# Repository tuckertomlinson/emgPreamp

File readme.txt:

#Boilerplate:
The files in this repository are my attempt to produce a high-quailty,
buffering amplifier for EMG signals in the laboratory environment. I
am NOT a hardware designer by trade and have not necessarily tested
any of the supplied files for my own purposes, much less yours. I 
make no garauntees that these circuits will be useful or even 
functional.

It is important to also note: I have not designed these
to comply with any FDA standards. Any compliance with said standards
is purely coincidental. These designs are inteded for animal research
and are NOT fit for human recordings in the clinical environment. 

If you choose to use these designs, it is incumbent on you to evaluate
the schematics and test them to ensure they are adequate, in both 
performance and safety, for your task.

I make no promise of support, however, you are welcome to shoot me
an email if you want to use these designs. I might be able to answer
some simple questions.

#The project:
-I need to record 24 differential EMG signals from intramuscular wires
-My signals of interest are in the +/-10mV range
-My ADC system has a +/-5V range, and is remote from the signal source
-I need to buffer and amplify my signals at the source to avoid line
artifacts in my recordings
-The source of the signal is a 50pin samtec 0.05" connector, which I 
	want to convert to something sane like a DB style connector
	so I can use standard cables with my amplified signals

#the solution:
-Signal source connects to a backplane card
-backplane has 6x16pin header sockets 
-each header socket accepts a daughter card that contains 4 differential channels
-Connection to external systems is via DB37 connector
  -24 signal out lines
  -GND and external power in (optional)
  -reference rail out
-daughter cards take:
  - 8 lines of input signal (4 differential signals), 
  - a ground rail, 
  - a power rail
    -the power rail should be in the 5-18V range
  -and a reference rail.
    -the reference rail should be ~ halfway between the ground and power rails
-daughter cards output:
  -4 lines of amplified differential signal centered on the reference rail
-Backplane has a 5pin header socket that is the source of the ground, power and reference rails
  -power connection to external systems will depend on the DAC format you use
  -for a 0V centered ADC (e.g. +/-5V), isolate the ground and power rails from the world, and short the reference to the ADC ground
  -for a positive biased ADC (e.g. 0-10V), connect the ground rail to the DAC ground, and the reference rail to one of the ADC inputs
    -logging the voltage of VRef allows you to subtract in software, recovering the true differential signal
  -The easiest power solution is to simply use 2x 9V batteries in series
    -Power rail is 18V, reference rail is 9V
  -included in the project is a schematic for a power conditioning card
    -card takes in 12-15V power
    -Isolates to internal 12V rail via switchmode isolation supply
    -Uses filters and linear regulators to supply 10V power rail and 5v reference rail to backplane
    -power rail, backplane ground and reference rail are isolated from the supplied power.

The circuit schematics for this project are built in Eagle. 
I have tried to label the lines in each PCB in a sane way, so it should be possible to sort out what's going on. 

In some cases I have needed to create a custom part based on other 
existing libraries in order to get the correct footprint and pinout. 
I have not explicitly included those libraries in this project.

Currently the backplane and daughter cards are tested and functioning as designed. With implanted EMG wires it is common to see single motor unit acticity in the EMG signal. The power-conditioning board is not yet tested

Tucker Tomlinson
tuckertomlinson@gmail.com
Jan 25 2017

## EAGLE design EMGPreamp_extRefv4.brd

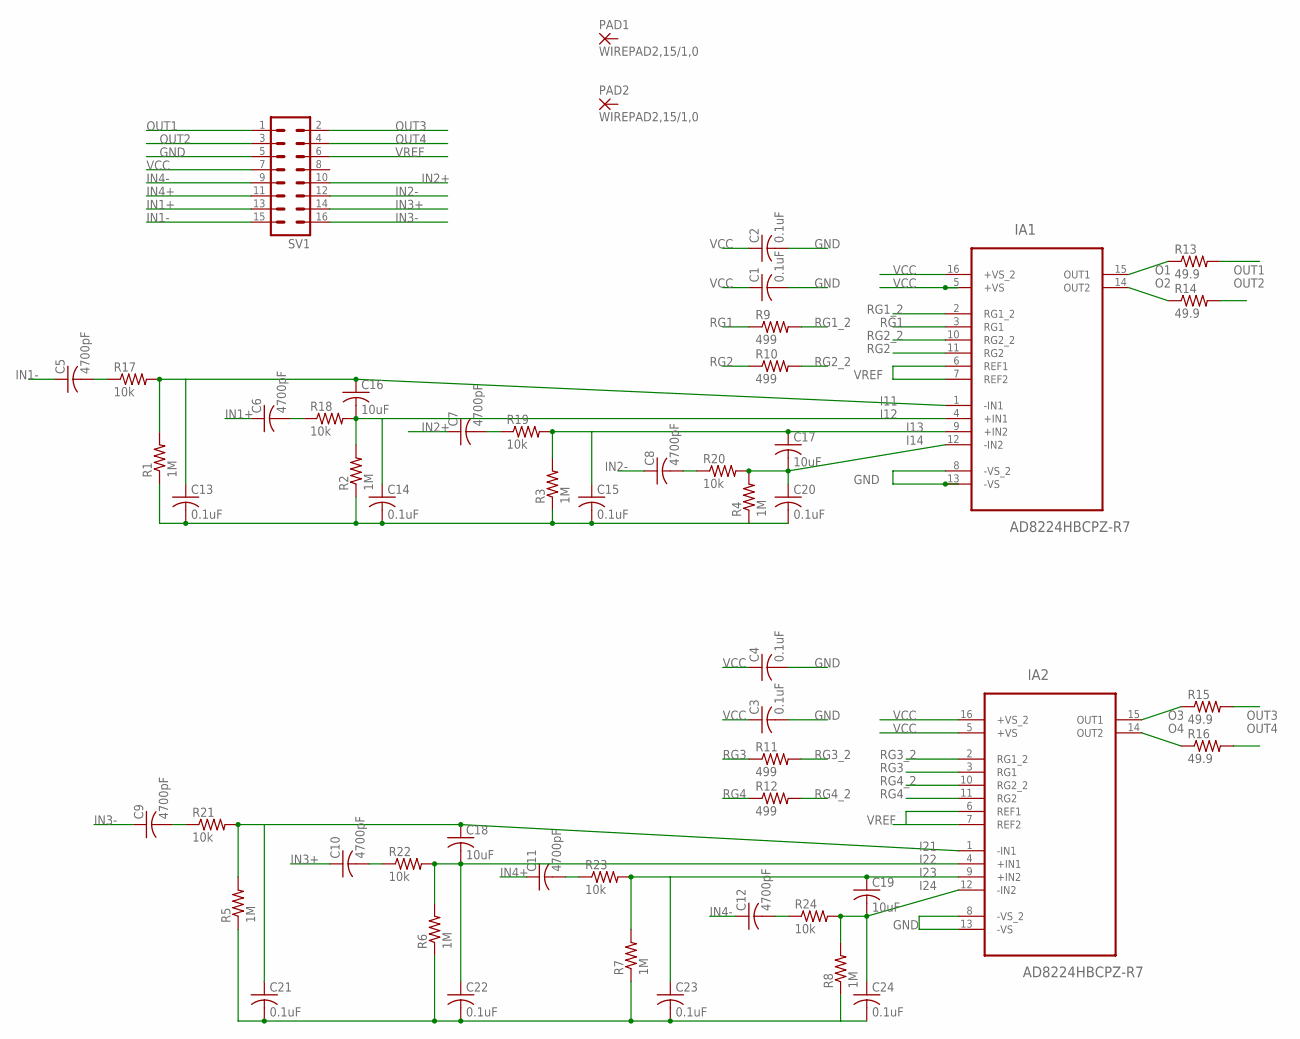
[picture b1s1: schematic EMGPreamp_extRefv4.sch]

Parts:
C1, C2, C3, C4, C13, C14, C15, C20, C21, C22, C23, C24: 0.1uF; C0805
C5, C6, C7, C8, C9, C10, C11, C12: 4700pF; C0805
C16, C17, C18, C19: 10uF; C0805
IA1, IA2: AD8224HBCPZ-R7; QFN65P400X400X100-16N
PAD1, PAD2: WIREPAD2,15/1,0; 2,15/1,0
R1, R2, R3, R4, R5, R6, R7, R8: 1M; R0805
R9, R10, R11, R12: 499; R0805
R13, R14, R15, R16: 49.9; R0805
R17, R18, R19, R20, R21, R22, R23, R24: 10k; R0805
SV1: MA08-2W

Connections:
GND: C1.2, C2.2, C3.2, C4.2, C13.2, C14.2, C15.2, C20.2, C21.2, C22.2, C23.2, C24.2, IA1.8 (-VS_2), IA1.13 (-VS), IA2.8 (-VS_2), IA2.13 (-VS), R1.1, R2.1, R3.1, R4.1, R5.1, R6.1, R7.1, R8.1, SV1.5
I11: C13.1, C16.1, IA1.1 (-IN1), R1.2, R17.2
I12: C14.1, C16.2, IA1.4 (+IN1), R2.2, R18.2
I13: C15.1, C17.1, IA1.9 (+IN2), R3.2, R19.2
I14: C17.2, C20.1, IA1.12 (-IN2), R4.2, R20.2
I21: C18.1, C21.1, IA2.1 (-IN1), R5.2, R21.2
I22: C18.2, C22.1, IA2.4 (+IN1), R6.2, R22.2
I23: C19.1, C23.1, IA2.9 (+IN2), R7.2, R23.2
I24: C19.2, C24.1, IA2.12 (-IN2), R8.2, R24.2
IN1+: C6.1, SV1.13
IN1-: C5.1, SV1.15
IN2+: C7.1, SV1.10
IN2-: C8.1, SV1.12
IN3+: C10.1, SV1.14
IN3-: C9.1, SV1.16
IN4+: C11.1, SV1.11
IN4-: C12.1, SV1.9
unnamed: C5.2, R17.1
unnamed: C6.2, R18.1
unnamed: C8.2, R20.1
unnamed: C9.2, R21.1
unnamed: C10.2, R22.1
unnamed: C7.2, R19.1
unnamed: C11.2, R23.1
unnamed: C12.2, R24.1
O1: IA1.15 (OUT1), R13.1
O2: IA1.14 (OUT2), R14.1
O3: IA2.15 (OUT1), R15.1
O4: IA2.14 (OUT2), R16.1
OUT1: R13.2, SV1.1
OUT2: R14.2, SV1.3
OUT3: R15.2, SV1.2
OUT4: R16.2, SV1.4
RG1: IA1.3 (RG1), R9.1
RG1_2: IA1.2 (RG1_2), R9.2
RG2: IA1.11 (RG2), R10.1
RG2_2: IA1.10 (RG2_2), R10.2
RG3: IA2.3 (RG1), R11.1
RG3_2: IA2.2 (RG1_2), R11.2
RG4: IA2.11 (RG2), R12.1
RG4_2: IA2.10 (RG2_2), R12.2
VCC: C1.1, C2.1, C3.1, C4.1, IA1.5 (+VS), IA1.16 (+VS_2), IA2.5 (+VS), IA2.16 (+VS_2), SV1.7
VREF: IA1.6 (REF1), IA1.7 (REF2), IA2.6 (REF1), IA2.7 (REF2), SV1.6

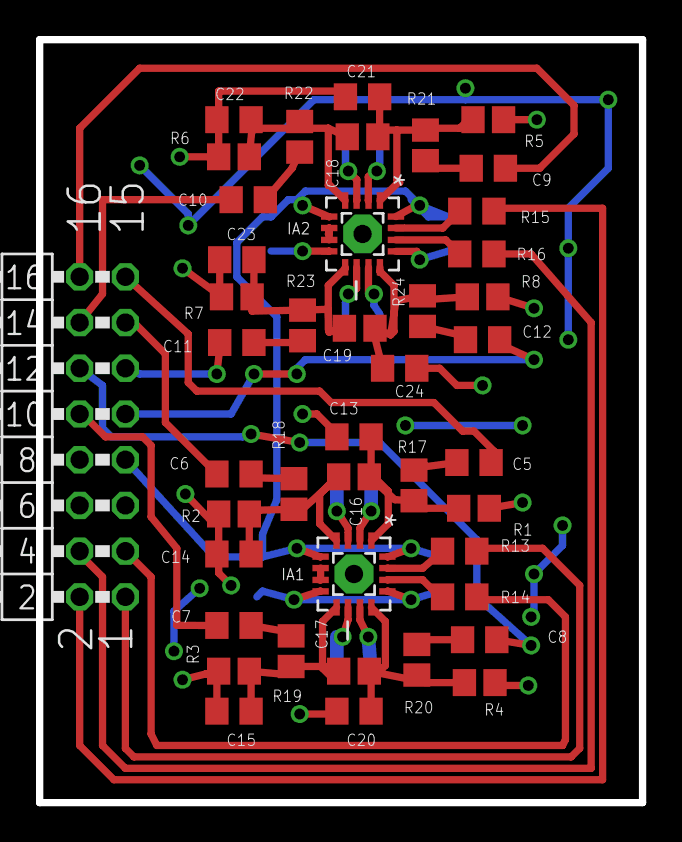
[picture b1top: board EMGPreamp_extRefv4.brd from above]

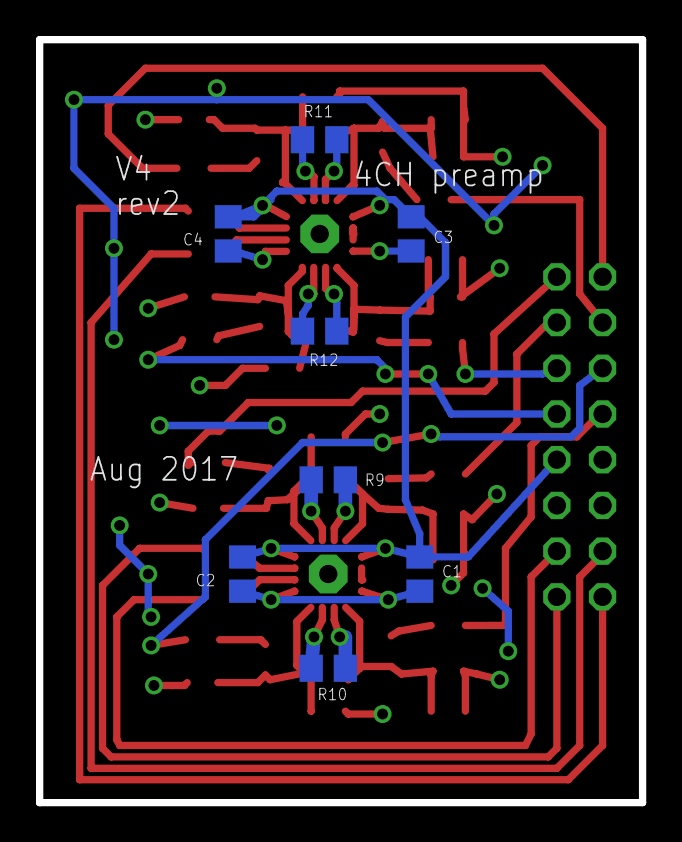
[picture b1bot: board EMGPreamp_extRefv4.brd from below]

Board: 2 copper layers, 33.5 x 42.4 mm, 53 parts (8 on the bottom side), 43 nets.

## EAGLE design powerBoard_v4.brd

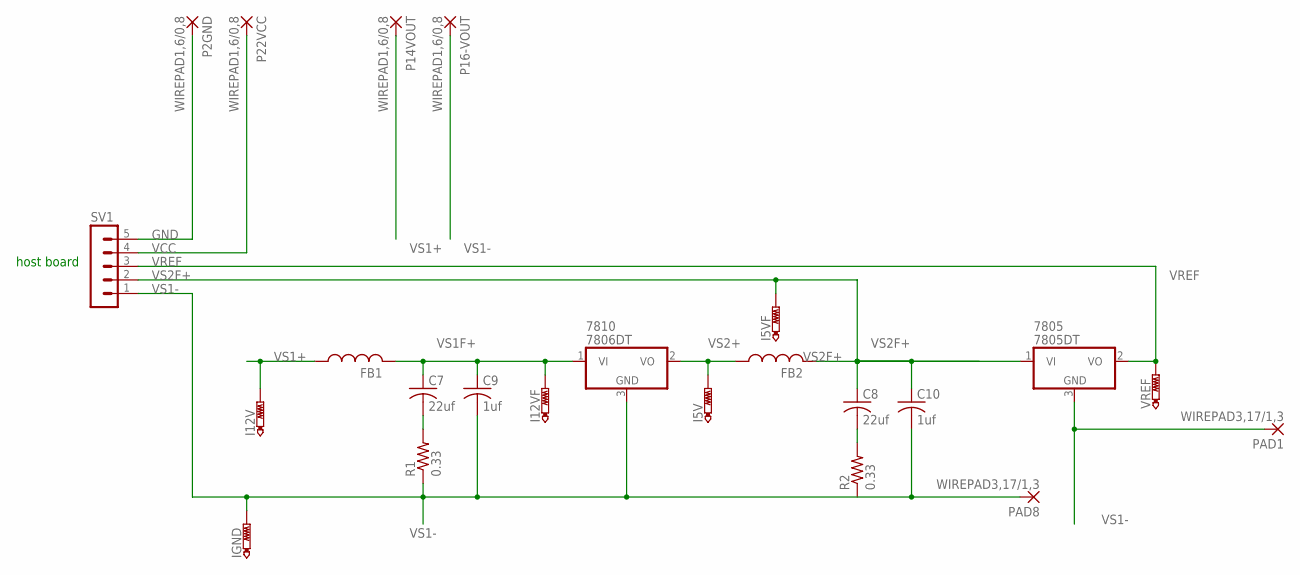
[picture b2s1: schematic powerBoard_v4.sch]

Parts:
7805: 7805DT; TO252
7810: 7806DT; TO252
C7, C8: 22uf; C0805K
C9, C10: 1uf; C0805K
FB1, FB2: L-USL2012C; L2012C
I5V, I5VF, I12V, I12VF: PTR1PAD1-13; P1-13
IGND: PTR1PAD1-13; P1-13
P2GND, P14VOUT, P16-VOUT, P22VCC: WIREPAD1,6/0,8; 1,6/0,8
PAD1, PAD8: WIREPAD3,17/1,3; 3,17/1,3
R1, R2: 0.33; R2012W
SV1: MA05-1
VREF: PTR1PAD1-13; P1-13

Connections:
GND: P2GND.1, SV1.5
unnamed: C8.2, R2.2
unnamed: C7.2, R1.2
VCC: P22VCC.1, SV1.4
VREF: 7805.2 (VO), SV1.3, VREF.TP
VS1+: FB1.1, I12V.TP, P14VOUT.1
VS1-: 7805.3 (GND), 7810.3 (GND), C9.2, C10.2, IGND.TP, P16-VOUT.1, PAD1.1, PAD8.1, R1.1, SV1.1
VS1F+: 7810.1 (VI), C7.1, C9.1, FB1.2, I12VF.TP
VS2+: 7810.2 (VO), FB2.1, I5V.TP
VS2F+: 7805.1 (VI), C8.1, C10.1, FB2.2, I5VF.TP, SV1.2

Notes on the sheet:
host board

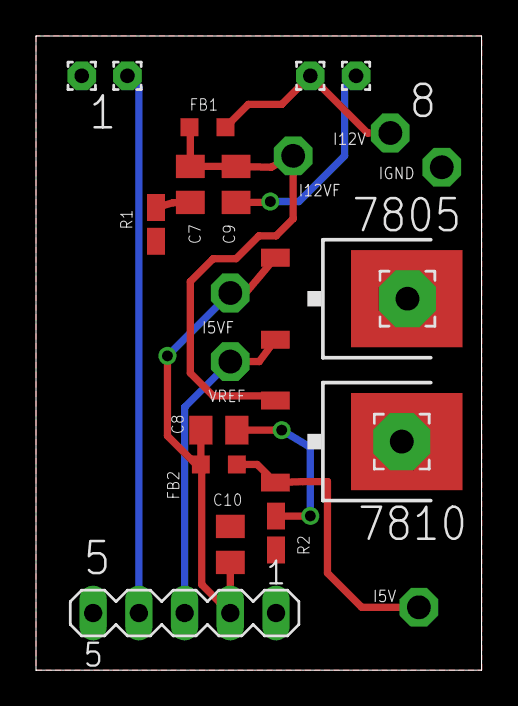
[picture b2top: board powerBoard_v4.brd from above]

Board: 2 copper layers, 24.8 x 35.2 mm, 23 parts (0 on the bottom side), 10 nets.

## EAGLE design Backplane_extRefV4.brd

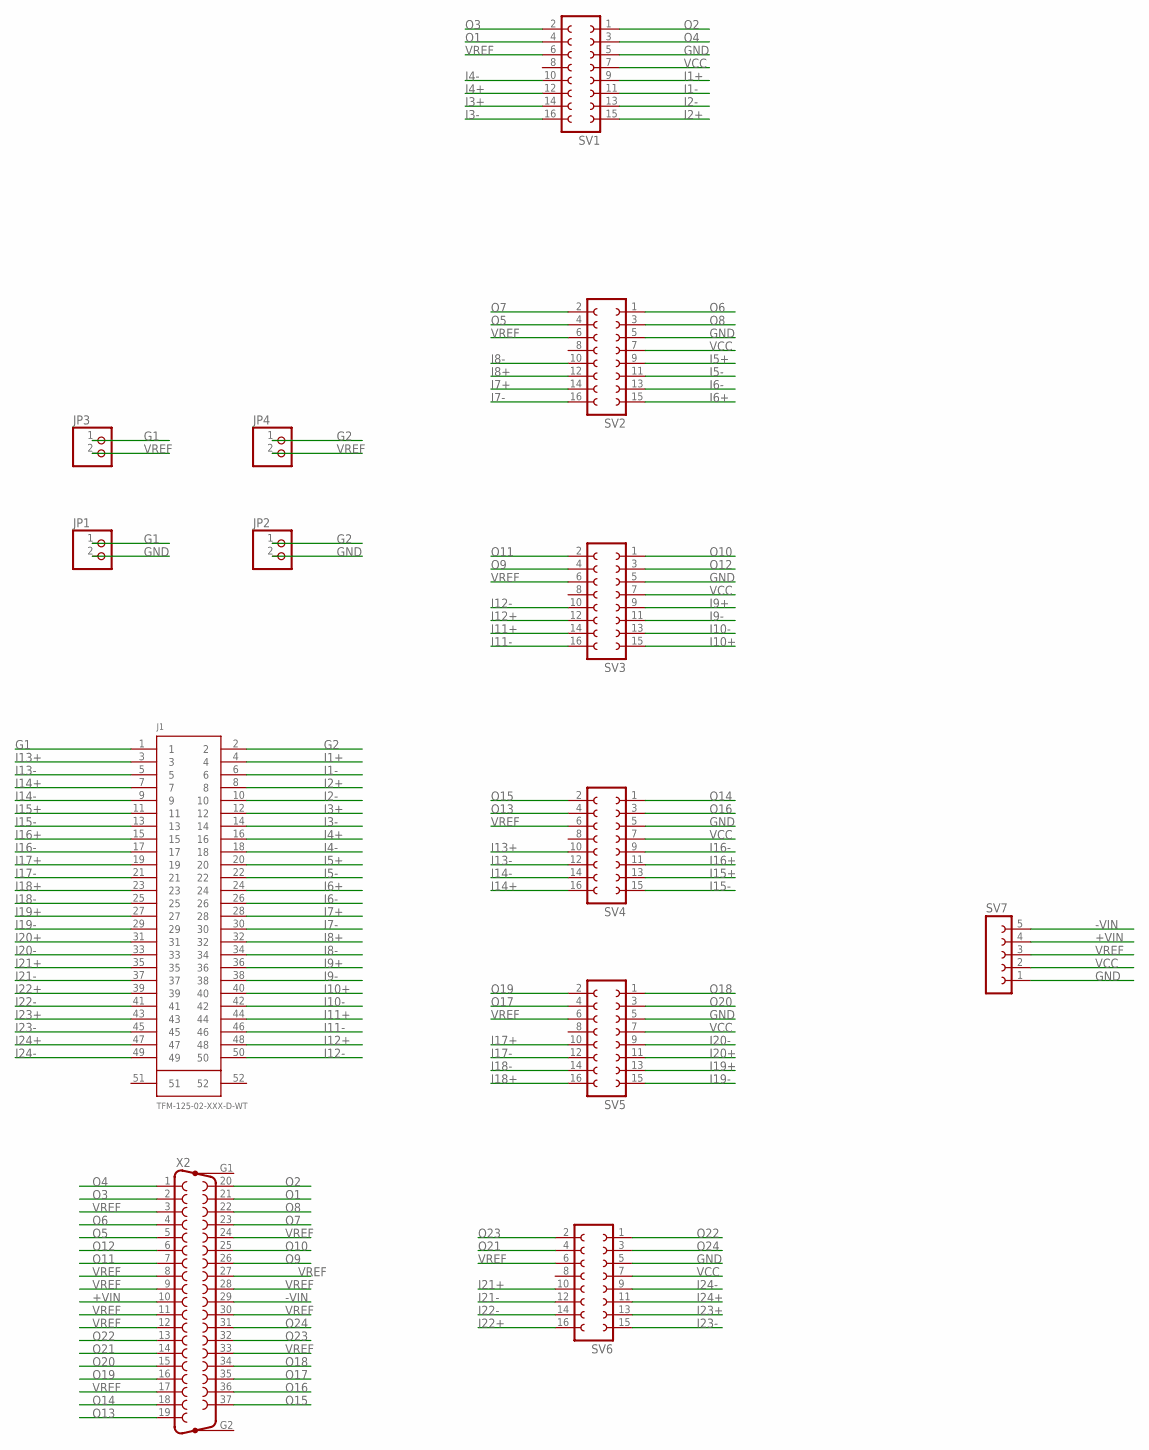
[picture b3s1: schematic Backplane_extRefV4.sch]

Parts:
J1: TFM-125-02-XXX-D-WT
JP1, JP2, JP3, JP4: PINHD-1X2; 1X02
SV1, SV2, SV3, SV4, SV5, SV6: FE08-2
SV7: FE05-1
X2: F37HP

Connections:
+VIN: SV7.4, X2.10
-VIN: SV7.5, X2.29
G1: J1.1, JP1.1, JP3.1
G2: J1.2, JP2.1, JP4.1
GND: JP1.2, JP2.2, SV1.5, SV2.5, SV3.5, SV4.5, SV5.5, SV6.5, SV7.1
I1+: J1.4, SV1.9
I1-: J1.6, SV1.11
I2+: J1.8, SV1.15
I2-: J1.10, SV1.13
I3+: J1.12, SV1.14
I3-: J1.14, SV1.16
I4+: J1.16, SV1.12
I4-: J1.18, SV1.10
I5+: J1.20, SV2.9
I5-: J1.22, SV2.11
I6+: J1.24, SV2.15
I6-: J1.26, SV2.13
I7+: J1.28, SV2.14
I7-: J1.30, SV2.16
I8+: J1.32, SV2.12
I8-: J1.34, SV2.10
I9+: J1.36, SV3.9
I9-: J1.38, SV3.11
I10+: J1.40, SV3.15
I10-: J1.42, SV3.13
I11+: J1.44, SV3.14
I11-: J1.46, SV3.16
I12+: J1.48, SV3.12
I12-: J1.50, SV3.10
I13+: J1.3, SV4.10
I13-: J1.5, SV4.12
I14+: J1.7, SV4.16
I14-: J1.9, SV4.14
I15+: J1.11, SV4.13
I15-: J1.13, SV4.15
I16+: J1.15, SV4.11
I16-: J1.17, SV4.9
I17+: J1.19, SV5.10
I17-: J1.21, SV5.12
I18+: J1.23, SV5.16
I18-: J1.25, SV5.14
I19+: J1.27, SV5.13
I19-: J1.29, SV5.15
I20+: J1.31, SV5.11
I20-: J1.33, SV5.9
I21+: J1.35, SV6.10
I21-: J1.37, SV6.12
I22+: J1.39, SV6.16
I22-: J1.41, SV6.14
I23+: J1.43, SV6.13
I23-: J1.45, SV6.15
I24+: J1.47, SV6.11
I24-: J1.49, SV6.9
O1: SV1.4, X2.21
O2: SV1.1, X2.20
O3: SV1.2, X2.2
O4: SV1.3, X2.1
O5: SV2.4, X2.5
O6: SV2.1, X2.4
O7: SV2.2, X2.23
O8: SV2.3, X2.22
O9: SV3.4, X2.26
O10: SV3.1, X2.25
O11: SV3.2, X2.7
O12: SV3.3, X2.6
O13: SV4.4, X2.19
O14: SV4.1, X2.18
O15: SV4.2, X2.37
O16: SV4.3, X2.36
O17: SV5.4, X2.35
O18: SV5.1, X2.34
O19: SV5.2, X2.16
O20: SV5.3, X2.15
O21: SV6.4, X2.14
O22: SV6.1, X2.13
O23: SV6.2, X2.32
O24: SV6.3, X2.31
VCC: SV1.7, SV2.7, SV3.7, SV4.7, SV5.7, SV6.7, SV7.2
VREF: JP3.2, JP4.2, SV1.6, SV2.6, SV3.6, SV4.6, SV5.6, SV6.6, SV7.3, X2.3, X2.8, X2.9, X2.11, X2.12, X2.17, X2.24, X2.27, X2.28, X2.30, X2.33

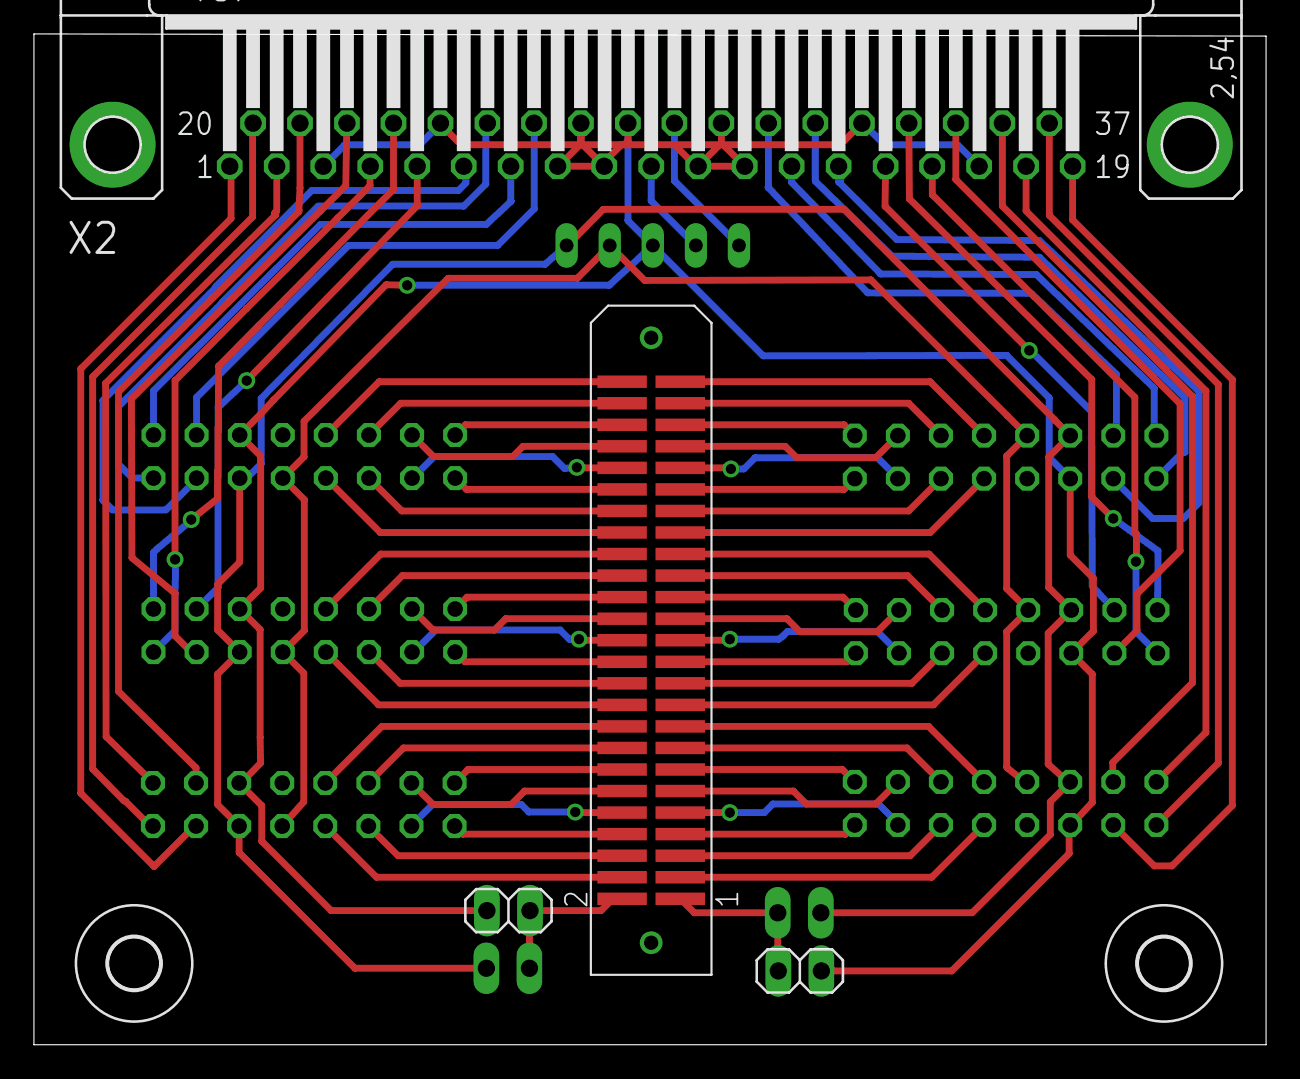
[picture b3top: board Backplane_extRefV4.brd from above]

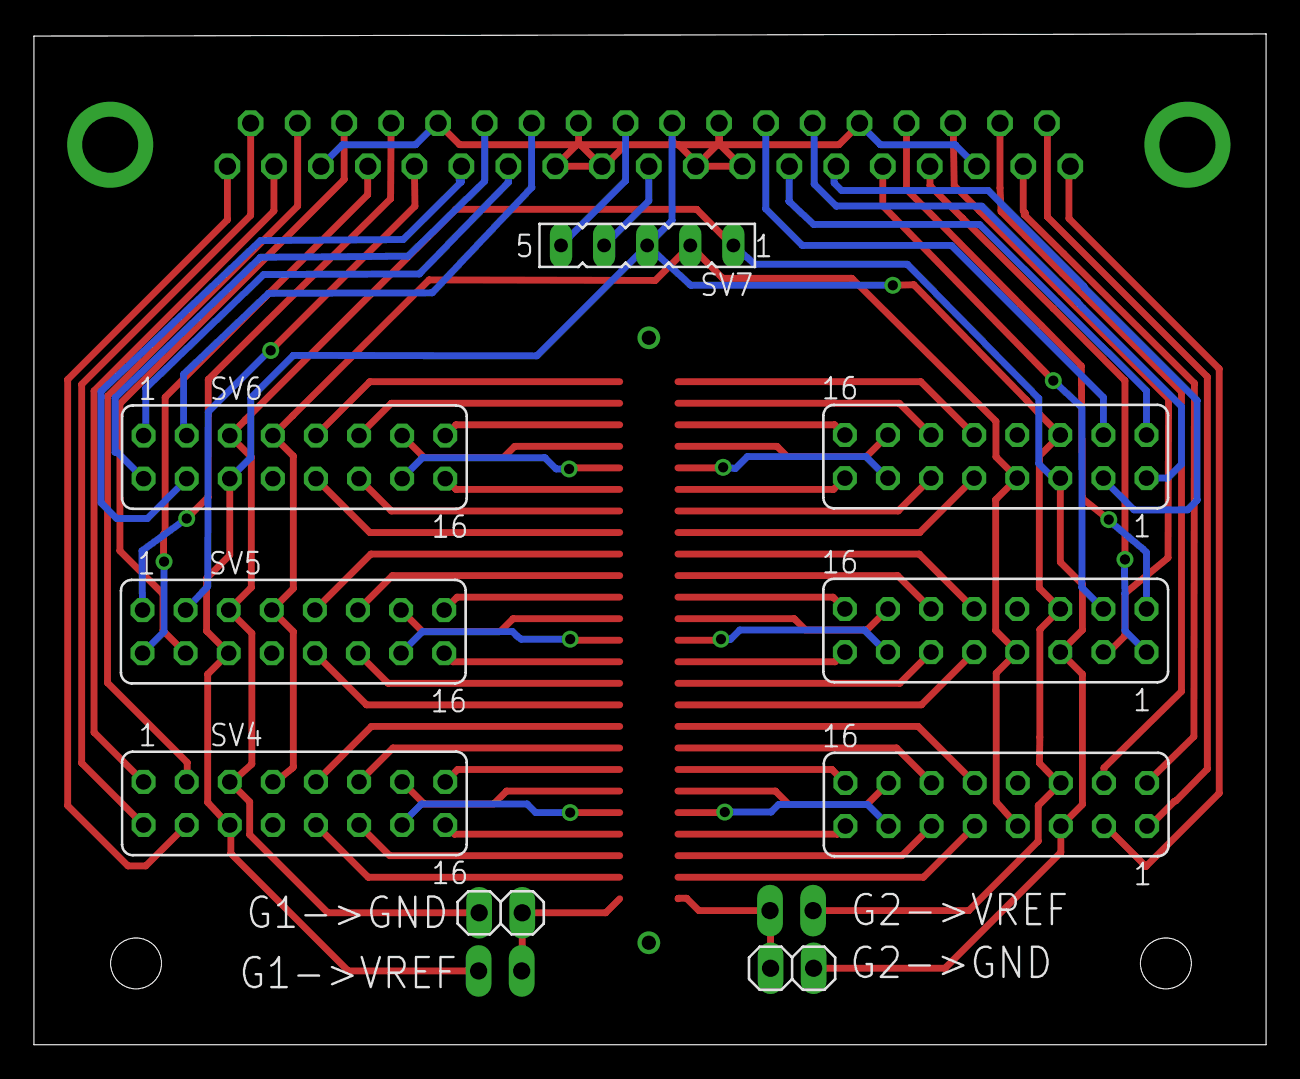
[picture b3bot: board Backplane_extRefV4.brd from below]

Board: 2 copper layers, 72.6 x 59.6 mm, 15 parts (9 on the bottom side), 79 nets.

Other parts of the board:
U$1, U$2: 3,0

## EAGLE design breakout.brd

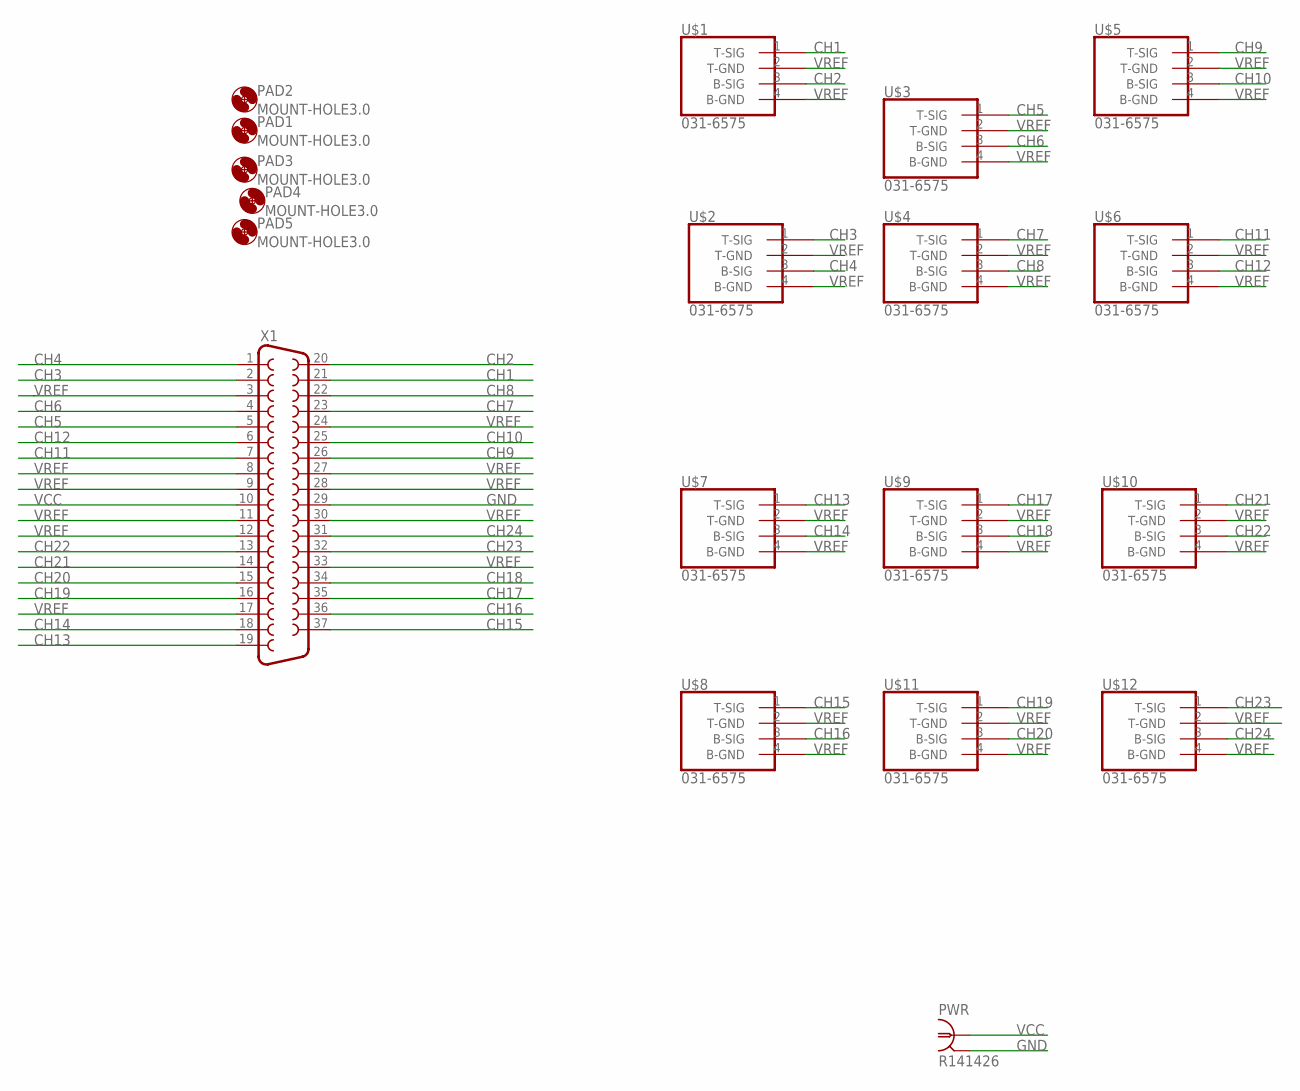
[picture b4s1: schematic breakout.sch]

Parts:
PAD1, PAD2, PAD3, PAD4, PAD5: MOUNT-HOLE3.0; 3,0
PWR: R141426
U$1, U$2, U$3, U$4, U$5, U$6, U$7, U$8, U$9, U$10, U$11, U$12: 031-6575
X1: F37HP

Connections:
CH1: U$1.1 (T-SIG), X1.21
CH2: U$1.3 (B-SIG), X1.20
CH3: U$2.1 (T-SIG), X1.2
CH4: U$2.3 (B-SIG), X1.1
CH5: U$3.1 (T-SIG), X1.5
CH6: U$3.3 (B-SIG), X1.4
CH7: U$4.1 (T-SIG), X1.23
CH8: U$4.3 (B-SIG), X1.22
CH9: U$5.1 (T-SIG), X1.26
CH10: U$5.3 (B-SIG), X1.25
CH11: U$6.1 (T-SIG), X1.7
CH12: U$6.3 (B-SIG), X1.6
CH13: U$7.1 (T-SIG), X1.19
CH14: U$7.3 (B-SIG), X1.18
CH15: U$8.1 (T-SIG), X1.37
CH16: U$8.3 (B-SIG), X1.36
CH17: U$9.1 (T-SIG), X1.35
CH18: U$9.3 (B-SIG), X1.34
CH19: U$11.1 (T-SIG), X1.16
CH20: U$11.3 (B-SIG), X1.15
CH21: U$10.1 (T-SIG), X1.14
CH22: U$10.3 (B-SIG), X1.13
CH23: U$12.1 (T-SIG), X1.32
CH24: U$12.3 (B-SIG), X1.31
GND: PWR.2, PWR.3 (2), PWR.4 (2), PWR.5 (2), X1.29
VCC: PWR.1, X1.10
VREF: U$1.2 (T-GND), U$1.4 (B-GND), U$2.2 (T-GND), U$2.4 (B-GND), U$3.2 (T-GND), U$3.4 (B-GND), U$4.2 (T-GND), U$4.4 (B-GND), U$5.2 (T-GND), U$5.4 (B-GND), U$6.2 (T-GND), U$6.4 (B-GND), U$7.2 (T-GND), U$7.4 (B-GND), U$8.2 (T-GND), U$8.4 (B-GND), U$9.2 (T-GND), U$9.4 (B-GND), U$10.2 (T-GND), U$10.4 (B-GND), U$11.2 (T-GND), U$11.4 (B-GND), U$12.2 (T-GND), U$12.4 (B-GND), X1.3, X1.8, X1.9, X1.11, X1.12, X1.17, X1.24, X1.27, X1.28, X1.30, X1.33

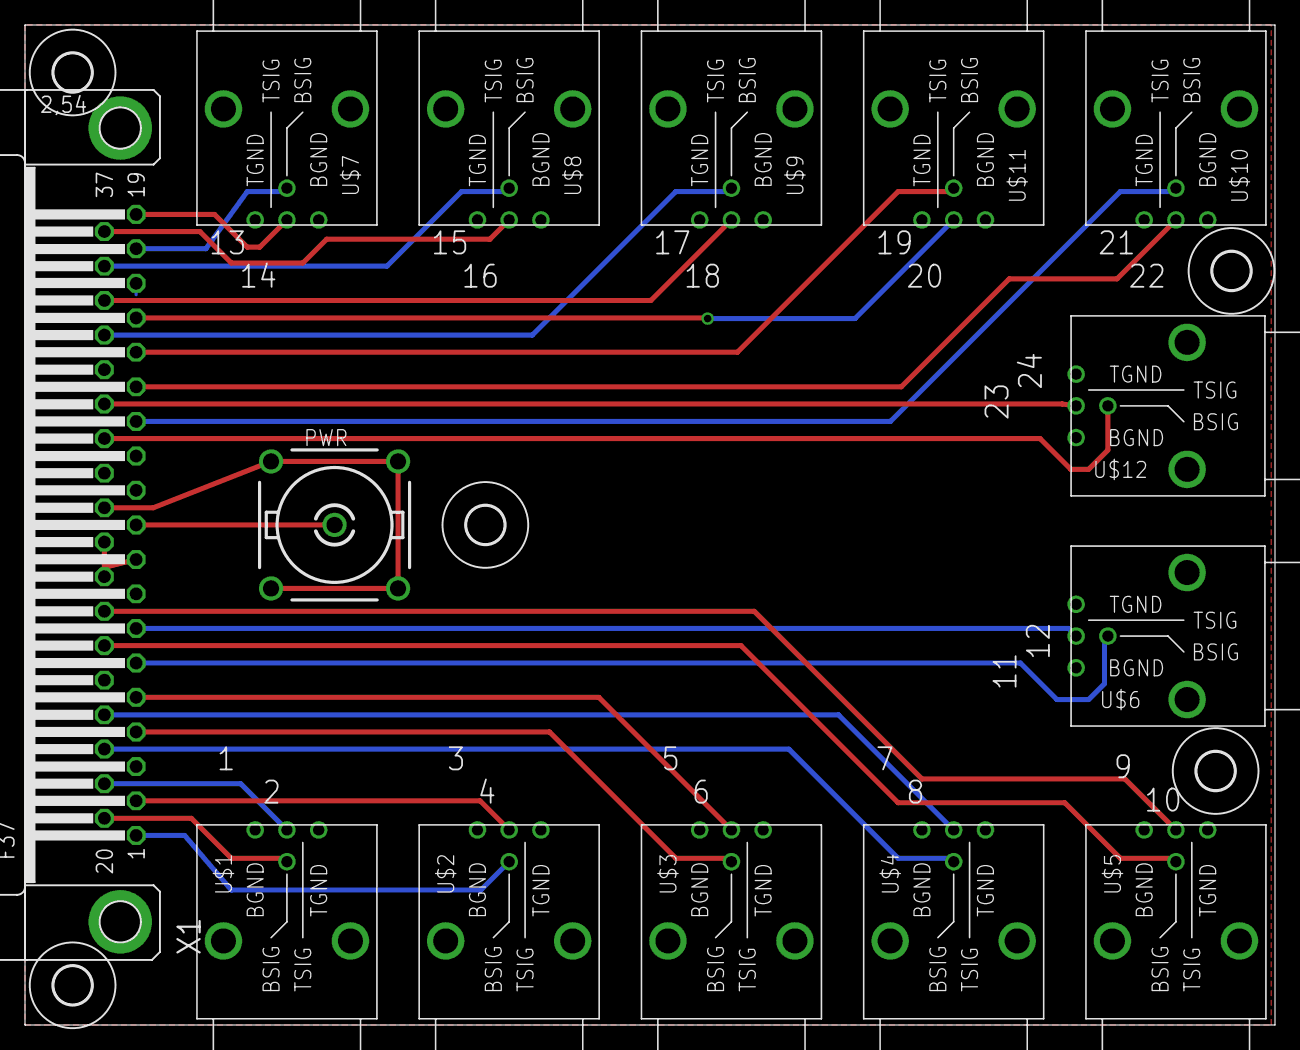
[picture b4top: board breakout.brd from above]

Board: 2 copper layers, 100.0 x 80.0 mm, 19 parts (0 on the bottom side), 27 nets.

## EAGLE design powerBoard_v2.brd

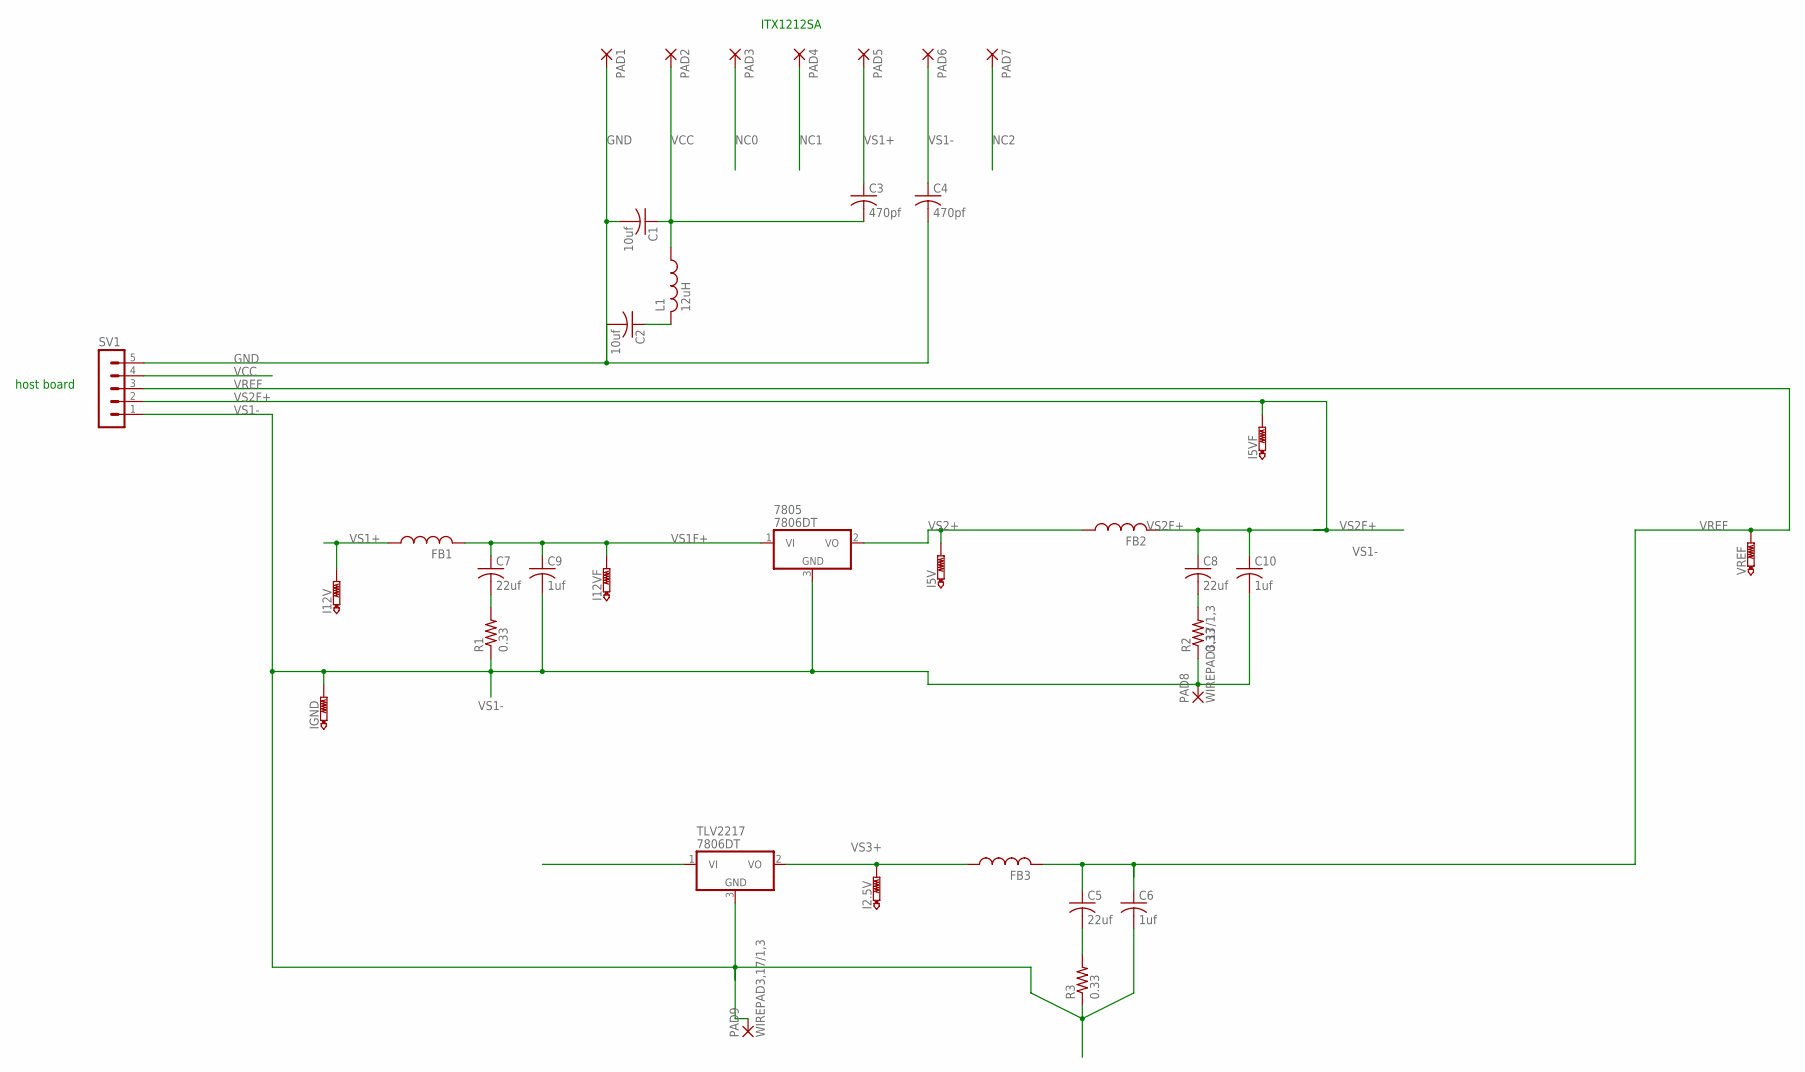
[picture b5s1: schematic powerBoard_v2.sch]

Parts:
7805: 7806DT; TO252
C1, C2: 10uf; C0805K
C3, C4: 470pf; C0805K
C5, C7, C8: 22uf; C0805K
C6, C9, C10: 1uf; C0805K
FB1, FB2, FB3: L-USL2012C; L2012C
I2.5V, I5V, I5VF, I12V, I12VF: PTR1PAD1-13; P1-13
IGND: PTR1PAD1-13; P1-13
L1: 12uH; L2012C
PAD1, PAD2, PAD3, PAD4, PAD5, PAD6, PAD7: SMD2; SMD1,27-2,54
PAD8, PAD9: WIREPAD3,17/1,3; 3,17/1,3
R1, R2, R3: 0.33; R2012W
SV1: MA05-1
TLV2217: 7806DT; TO252
VREF: PTR1PAD1-13; P1-13

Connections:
GND: C1.2, C2.2, C4.2, PAD1.1, SV1.5
unnamed: C2.1, L1.2
unnamed: C5.2, R3.2
unnamed: C8.2, R2.2
unnamed: C7.2, R1.2
NC0: PAD3.1
NC1: PAD4.1
NC2: PAD7.1
VCC: C1.1, C3.2, L1.1, PAD2.1, SV1.4
VREF: C5.1, C6.1, FB3.2, SV1.3, VREF.TP
VS1+: C3.1, FB1.1, I12V.TP, PAD5.1
VS1-: 7805.3 (GND), C4.1, C6.2, C9.2, C10.2, IGND.TP, PAD6.1, PAD8.1, PAD9.1, R1.1, R2.1, R3.1, SV1.1, TLV2217.3 (GND)
VS1F+: 7805.1 (VI), C7.1, C9.1, FB1.2, I12VF.TP, TLV2217.1 (VI)
VS2+: 7805.2 (VO), FB2.1, I5V.TP
VS2F+: C8.1, C10.1, FB2.2, I5VF.TP, SV1.2
VS3+: FB3.1, I2.5V.TP, TLV2217.2 (VO)

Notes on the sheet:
ITX1212SA
host board

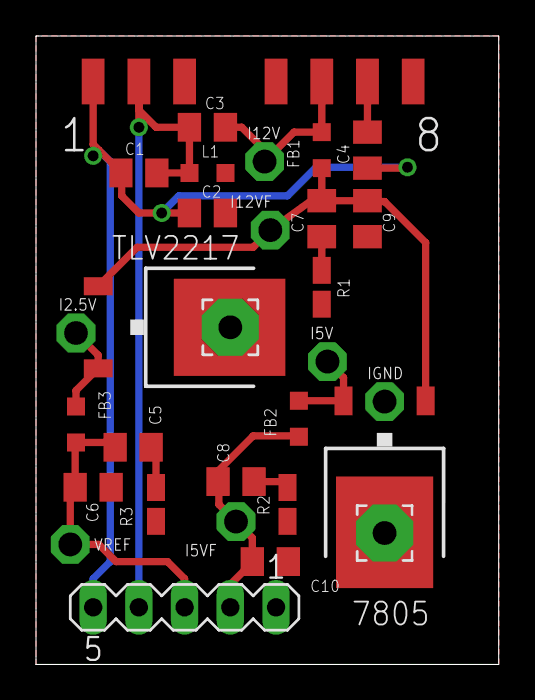
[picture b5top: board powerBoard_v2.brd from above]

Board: 2 copper layers, 25.7 x 34.9 mm, 36 parts (0 on the bottom side), 13 nets.

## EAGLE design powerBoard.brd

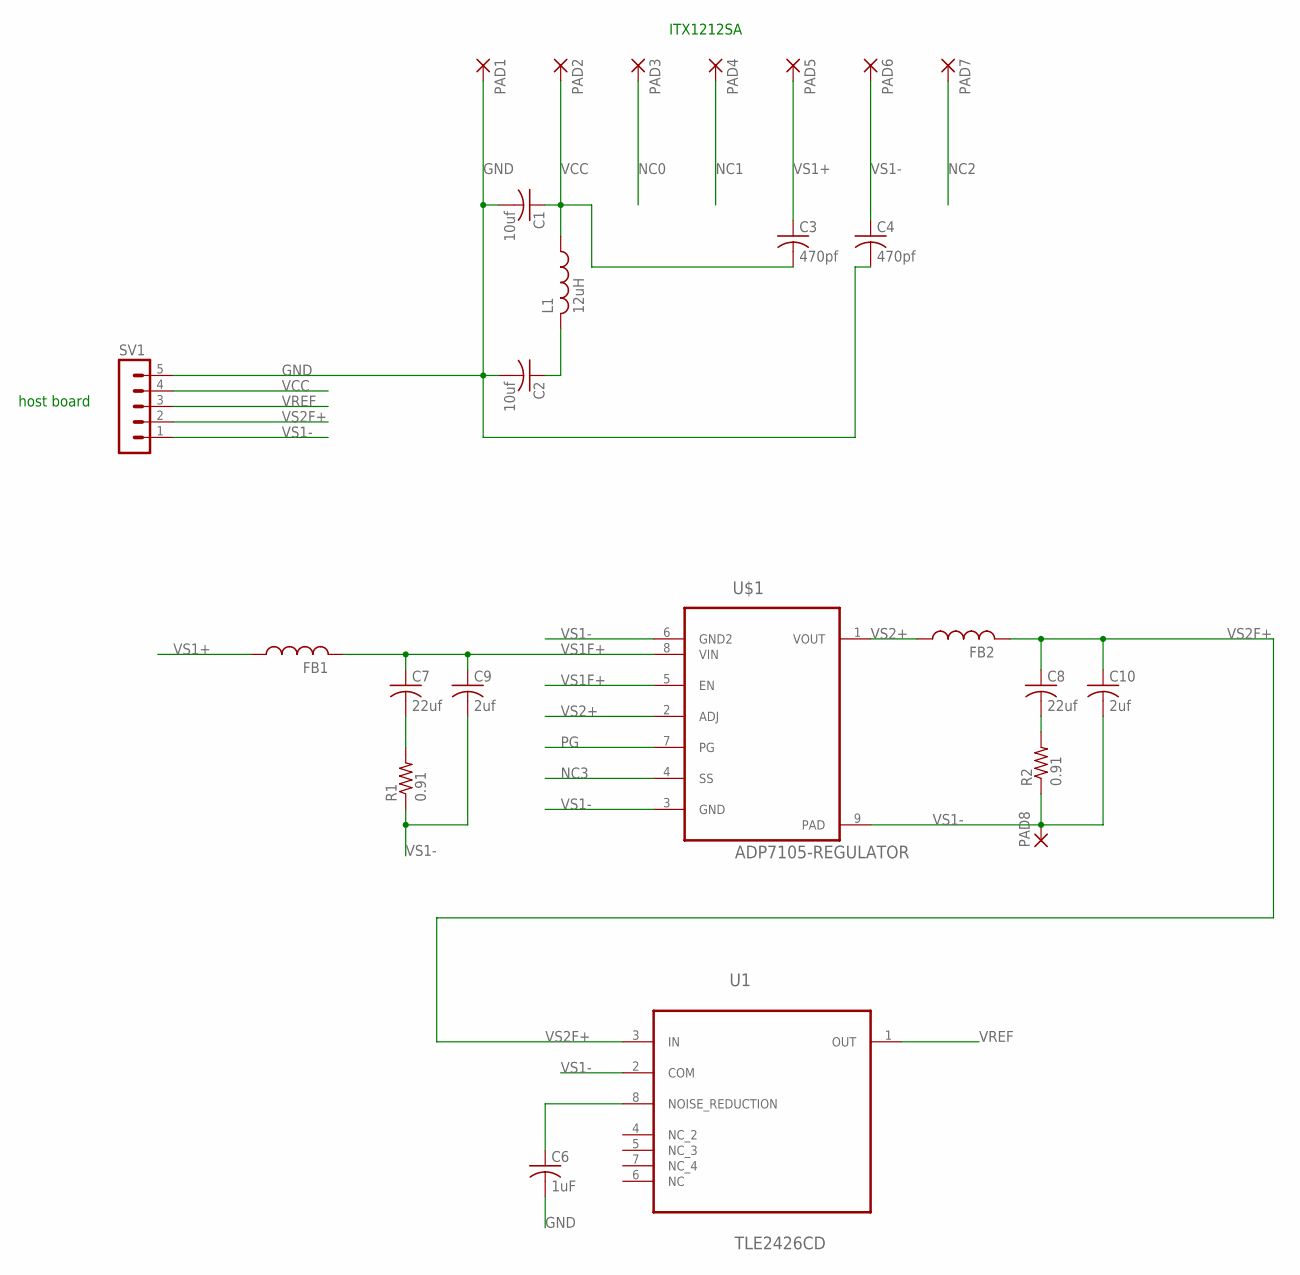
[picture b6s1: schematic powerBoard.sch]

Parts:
C1, C2: 10uf; C0805K
C3, C4: 470pf; C0805K
C6: 1uF; C0805
C7, C8: 22uf; C0805K
C9, C10: 2uf; C0805K
FB1, FB2: L-USL2012C; L2012C
L1: 12uH; L2012C
PAD1, PAD2, PAD3, PAD4, PAD5, PAD6, PAD7: SMD2; SMD1,27-2,54
PAD8: 2,54/1,1
R1, R2: 0.91; R2012W
SV1: MA05-1
U1: TLE2426CD; SOIC127P600X175-8N
U$1: ADP7105-REGULATOR

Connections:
GND: C1.2, C2.2, C4.2, C6.2, PAD1.1, SV1.5
unnamed: C2.1, L1.2
unnamed: C6.1, U1.8 (NOISE_REDUCTION)
unnamed: C8.2, R2.2
unnamed: C7.2, R1.2
NC0: PAD3.1
NC1: PAD4.1
NC2: PAD7.1
NC3: U$1.4 (SS)
PG: U$1.7 (PG)
VCC: C1.1, C3.2, L1.1, PAD2.1, SV1.4
VREF: SV1.3, U1.1 (OUT)
VS1+: C3.1, FB1.1, PAD5.1
VS1-: C4.1, C9.2, C10.2, PAD6.1, PAD8.1, R1.1, R2.1, SV1.1, U1.2 (COM), U$1.3 (GND), U$1.6 (GND2), U$1.9 (PAD)
VS1F+: C7.1, C9.1, FB1.2, U$1.5 (EN), U$1.8 (VIN)
VS2+: FB2.1, U$1.1 (VOUT), U$1.2 (ADJ)
VS2F+: C8.1, C10.1, FB2.2, SV1.2, U1.3 (IN)

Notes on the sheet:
ITX1212SA
host board

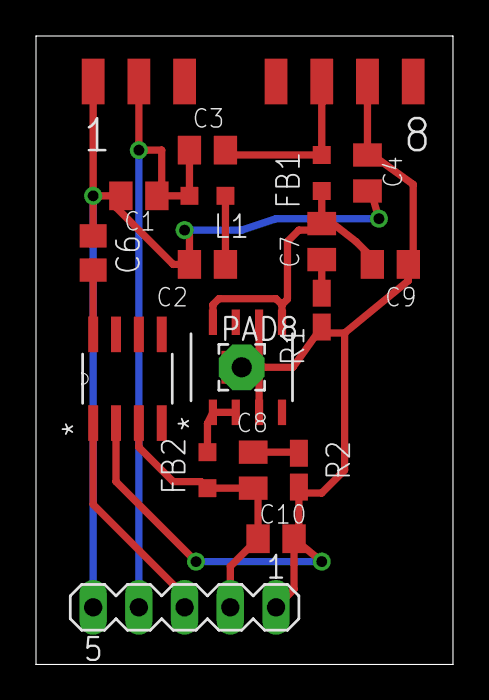
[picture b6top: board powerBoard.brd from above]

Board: 2 copper layers, 23.2 x 34.9 mm, 25 parts (0 on the bottom side), 12 nets.
